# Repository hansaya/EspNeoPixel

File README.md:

# EspNeoPixel

Esp32 based neo pixel driver designed to work with WLED. 

# Thoughts behind my design
I recently discovered that [wled project](https://github.com/Aircoookie/WLED) works with [hyperion](https://hyperion-project.org/) and sparked my interest in building a unified system to tick off all the requirements. From previous experience with neo pixels, I knew I had to make sure to have a good power supply and a good logic level conversion to run the leds reliably. Power supply is the biggest thing to tackle and for it I have tried many off the shelve converters but most either bulky or cannot run at specified rating. You could buy a AC to DC converts thats rated for the led without using dc-dc converter but either they are expensive or have to compromise in quality. I decided to design my board around ~20V input because I have many old laptop power bricks collecting dust that can handle at least 100W each. They are safe and can find in many shape and sizes. If you don't have one, you can easily obtain one through ebay. 

Features:
* Buck converter, 8-24V input to 5v or 12v output to drive the led strips.
* Up to 10A output current.
* Level converter to drive the data and clock singles at 5v.
* Button connected to GPIO0. This can be used within wled to turn off the output.
* Capability to turn off the output using wled relay output.
* Push in terminal connectors for quick connections.

# Board

Use zip file within /cam folder to fabricate the board using your favorite pcb house. Bom contains the parts list. Please note, I have not listed out all parts since I had most 0603 jelly beans parts at home. Use the schematic to get the full list.

Enjoy!

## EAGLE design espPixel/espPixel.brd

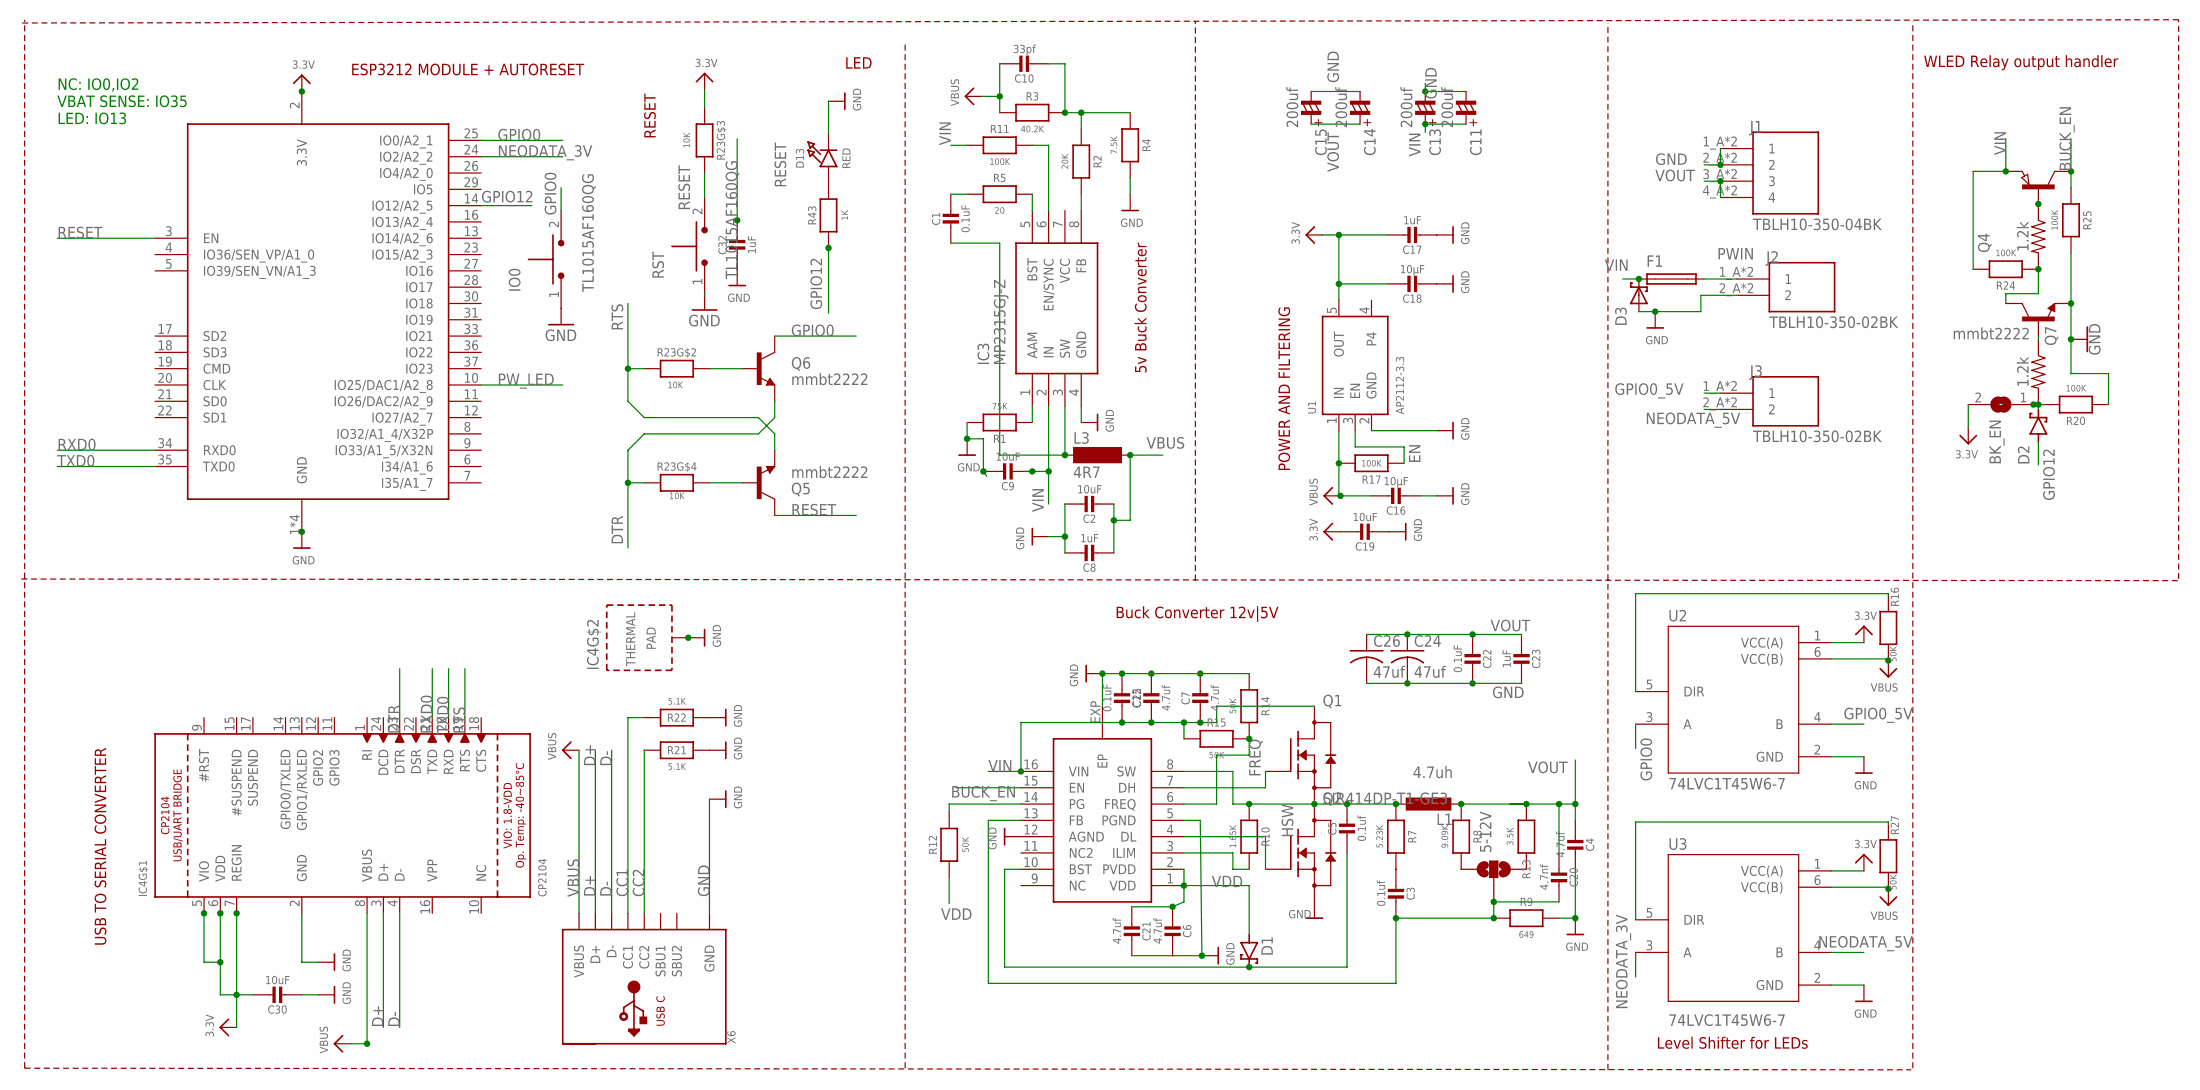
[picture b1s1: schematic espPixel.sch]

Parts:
5-12V: JUMPER-SMT_3_NO_NO-SILK; SMT-JUMPER_3_NO_NO-SILK
BK_EN: SJ
C1, C22, C25: 0.1uF; 0603-NO@1
C2: 10uF; 0603-NO@1
C3, C5: 0.1uf; 0603-NO@1
C4, C7, C12: 4.7uf; 0805_10MGAP
C6, C21: 4.7uf; 0603-NO@1
C8, C17, C23, C32: 1uF; 0603-NO@1
C9: 10uF; 0805_10MGAP
C10: 33pf; 0603-NO@1
C11, C13, C14, C15: 200uf; CSV-E/F
C16, C18: 10µF; 0805-NO
C19, C30: 10uF; 0805-NO
C20: 4.7nf; 0603-NO@1
C24, C26: 47uf; C3225
D1, D2: BAT60J; SOD323_ST
D3: SCHOTTKY-DIODESMC; SMC
D13: RED; CHIPLED_0805_NOOUTLINE
F1: SMD-MICRO-FUSE-BLOCK; OMNIBLOK
IC3: MP2315GJ-Z; SOT65P280X100-8N
IC4: CP2104; QFN24_4MM_SMSC
IO0: TL1015AF160QG; SW_TL1015AF160QG
J1: TBLH10-350-04BK; CUI_TBLH10-350-04BK
J2, J3: TBLH10-350-02BK; CUI_TBLH10-350-02BK
L1: 4.7uh; CEP125
L3: 4R7; MS50
Q1, Q2: SIR414DP-T1-GE3; TRANS_SQJ461EP-T1-GE3
Q4: PNP-TRANSISTOR_SOT23; SOT23
Q5, Q6, Q7: mmbt2222; SOT23-3
R1: 75K; 0603-NO
R2: 20K; 0603-NO
R3: 40.2K; 0603-NO
R4: 7.5K; 0603-NO
R5: 20; 0603-NO
R6, R19: 1.2k; 0603
R7: 5.23K; 0603-NO
R8: 9.09K; 0603-NO
R9: 649; 0603-NO
R10: 1.65K; 0603-NO
R11, R17, R20, R24, R25: 100K; 0603-NO
R12, R14, R15, R16, R27: 50K; 0603-NO
R13: 3.5K; 0603-NO
R21, R22: 5.1K; 0603-NO
R23: 10K; RESPACK_4X0603
R43: 1K; 0603-NO
RST: TL1015AF160QG; SW_TL1015AF160QG
U1: AP2112-3.3; SOT23-5
U2, U3: 74LVC1T45W6-7; SOT95P285X140-6N
U$1: MIC2101QFN16; QFN16
X6: USB_C; USB_C_CUSB31-CFM2AX-01-X
X8: ESP32_WROOM32_SKINNY; WROOM32_SKINNY

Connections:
3.3V: BK_EN.2, C17.1, C18.1, C19.1, C30.1, IC4.5 (VIO), IC4.6 (VDD), IC4.7 (REGIN), R23.3 (1), U1.5 (OUT), U2.1 (VCC(A)), U3.1 (VCC(A)), X8.2 (3.3V)
BUCK_EN: Q4.3 (C), R25.1, U$1.15 (EN)
CC1: R22.2, X6.A5 (CC1)
CC2: R21.2, X6.B5 (CC2)
D+: IC4.3 (D+), X6.A6 (D+), X6.B6 (D+)
D-: IC4.4 (D-), X6.A7 (D-), X6.B7 (D-)
DTR: IC4.23 (DTR), Q6.2 (E), R23.4 (1)
EN: R17.1, U1.3 (EN)
FREQ: R14.2, R15.2, U$1.6 (FREQ)
GND: C2.1, C4.1, C6.1, C7.1, C8.1, C9.1, C11.-, C12.1, C13.-, C14.-, C15.-, C16.2, C17.2, C18.2, C19.2, C21.1, C22.1, C23.1, C24.2, C25.2, C26.2, C30.2, C32.2, D3.A, D13.C, IC3.4 (GND), IC4.2 (GND), IC4.THERM (TP), IO0.1, J1.1_A (1), J1.1_B (1), J1.2_A (2), J1.2_B (2), J2.2_A (2), J2.2_B (2), Q2.1 (S), Q2.2 (S), Q2.3 (S), Q7.2 (E), R1.2, R4.2, R9.2, R14.1, R20.1, R21.1, R22.1, R25.2, RST.1, U1.2 (GND), U2.2 (GND), U3.2 (GND), U$1.5 (PGND), U$1.12 (AGND), U$1.EXP (EP), X6.A1B12 (GND), X6.B1A12 (GND), X8.1 (GND), X8.15 (GND), X8.38 (GND), X8.P$1 (GND)
GPIO0: IO0.2, Q6.3 (C), U2.3 (A), X8.25 (IO0/A2_1)
GPIO0_5V: J3.1_A (1), J3.1_B (1), U2.4 (B)
GPIO12: D2.A, R43.1, X8.14 (IO12/A2_5)
HSW: C5.1, L1.1, Q1.1 (S), Q1.2 (S), Q1.3 (S), Q2.5 (D), Q2.6 (D), Q2.7 (D), Q2.8 (D), Q2.9 (D), R7.1, R10.1, U$1.8 (SW)
unnamed: IC3.8 (FB), R2.2
unnamed: C10.2, R2.1, R3.2, R4.1
unnamed: IC3.5 (BST), R5.2
unnamed: IC3.1 (AAM), R1.1
unnamed: IC3.6 (EN/SYNC), R11.2
unnamed: C1.1, R5.1
unnamed: R12.2, U$1.14 (PG)
unnamed: C3.2, R7.2
unnamed: BK_EN.1, D2.C, R6.2, R20.2
unnamed: R27.1, U3.5 (DIR)
unnamed: 5-12V.2, C3.1, C20.1, R9.1, U$1.13 (FB)
unnamed: Q2.4 (G), U$1.4 (DL)
unnamed: Q1.4 (G), U$1.7 (DH)
unnamed: R10.2, U$1.3 (ILIM)
unnamed: C5.2, D1.C, U$1.10 (BST)
unnamed: 5-12V.1, R8.2
unnamed: 5-12V.3, R13.2
unnamed: D13.A, R43.2
unnamed: Q7.1 (B), R6.1
unnamed: Q4.1 (B), R19.1
unnamed: C1.2, IC3.3 (SW), L3.1
unnamed: Q7.3 (C), R19.2, R24.1
unnamed: R16.1, U2.5 (DIR)
unnamed: Q5.1 (B), R23.5 (2)
unnamed: Q6.1 (B), R23.7 (2)
NEODATA_3V: U3.3 (A), X8.24 (IO2/A2_2)
NEODATA_5V: J3.2_A (2), J3.2_B (2), U3.4 (B)
PWIN: F1.P$1 (1), J2.1_A (1), J2.1_B (1)
PW_LED: X8.10 (IO25/DAC1/A2_8)
RESET: C32.1, Q5.3 (C), R23.6 (2), RST.2, X8.3 (EN)
RTS: IC4.19 (RTS), Q5.2 (E), R23.2 (1)
RXD0: IC4.21 (TXD), X8.34 (RXD0)
TXD0: IC4.20 (RXD), X8.35 (TXD0)
VBUS: C2.2, C8.2, C10.1, C16.1, IC4.8 (VBUS), L3.2, R3.1, R16.2, R17.2, R27.2, U1.1 (IN), U2.6 (VCC(B)), U3.6 (VCC(B)), X6.A4B9 (VBUS), X6.B4A9 (VBUS)
VDD: C6.2, C21.2, D1.A, R12.1, U$1.1 (VDD), U$1.2 (PVDD)
VIN: C7.2, C9.2, C11.+, C12.2, C13.+, C25.1, D3.C, F1.P$2 (2), IC3.2 (IN), Q1.5 (D), Q1.6 (D), Q1.7 (D), Q1.8 (D), Q1.9 (D), Q4.2 (E), R11.1, R15.1, R24.2, U$1.16 (VIN)
VOUT: C4.2, C14.+, C15.+, C20.2, C22.2, C23.2, C24.1, C26.1, J1.3_A (3), J1.3_B (3), J1.4_A (4), J1.4_B (4), L1.2, R8.1, R13.1

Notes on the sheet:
5v Buck Converter
POWER AND FILTERING
ESP3212 MODULE + AUTORESET
NC: IO0,IO2 VBAT SENSE: IO35 LED: IO13
USB TO SERIAL CONVERTER
RESET
LED
Buck Converter 12v|5V
Level Shifter for LEDs
WLED Relay output handler

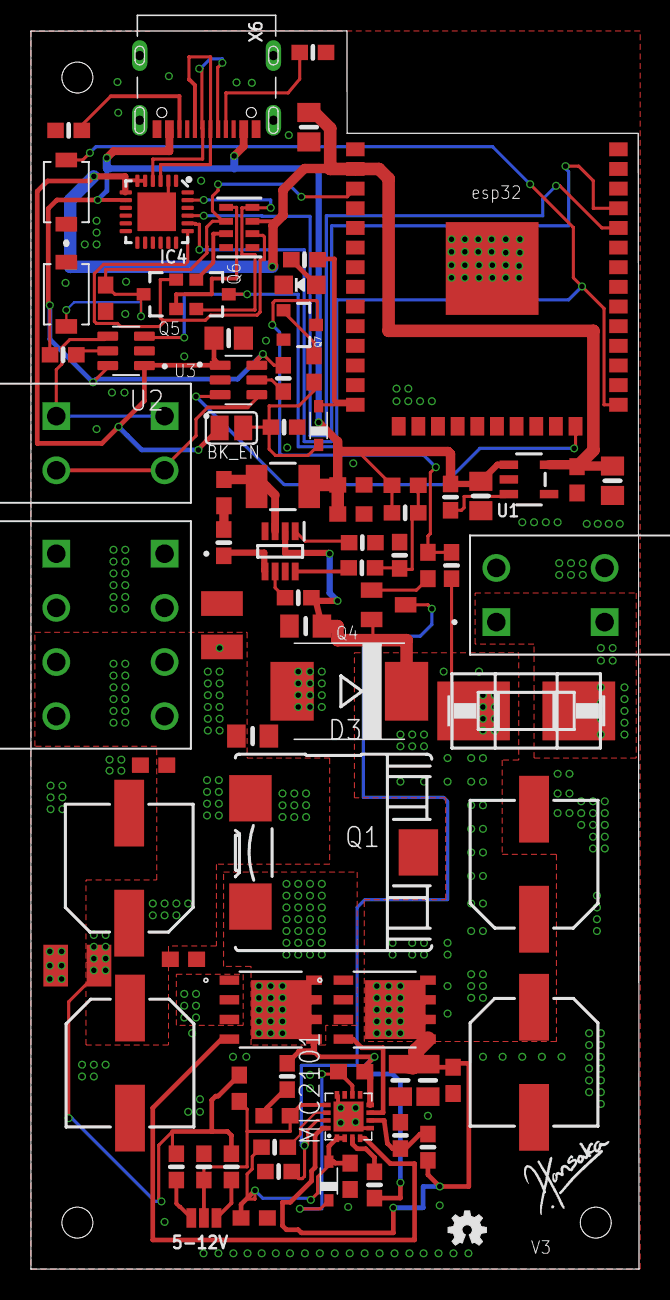
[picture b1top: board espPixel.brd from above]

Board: 2 copper layers, 39.3 x 80.0 mm, 84 parts (0 on the bottom side), 50 nets.

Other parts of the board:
U$30: OSHW-LOGO-MINI
U$33: SIGNATURE

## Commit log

2020-07-01 final board files
2020-07-01 remove version files
2020-07-14 bug fix
2020-07-14 Text clean up
2020-07-14 tunining
2020-07-14 parts list update
2020-07-15 ability to turn off the output
2020-07-16 eagle libs
2020-07-16 bigger caps
2020-07-22 clean up
2020-07-29 Create LICENSE
2020-07-30 finalizing the design
2020-07-30 pictures
2020-07-30 doc update
2020-08-06 final v2
2020-09-18 More filter caps
2020-12-16 v2 ideas
2021-01-07 v3 more compact size

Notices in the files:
parts and their libraries:
rc-master-smd: Copyright (C) 2007-2008, Bob Starr
SparkFun-Jumpers: Licensing: Creative Commons ShareAlike 4.0 International - https://creativecommons.org/licenses/by-sa/4.0
SparkFun: Licensing: CC v3.0 Share-Alike You are welcome to use this library for commercial purposes.
